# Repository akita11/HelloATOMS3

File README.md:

# HelloATOMS3

ATOMS3を使ったｽﾀｯｸﾁｬﾝ的な顔表示＋簡単なはんだ付けボード製作＋UIFlow2でのプログラミングのセットのハンズオン資料です。

## Author

Junichi Akita (akita@ifdl.jp, @akita11)

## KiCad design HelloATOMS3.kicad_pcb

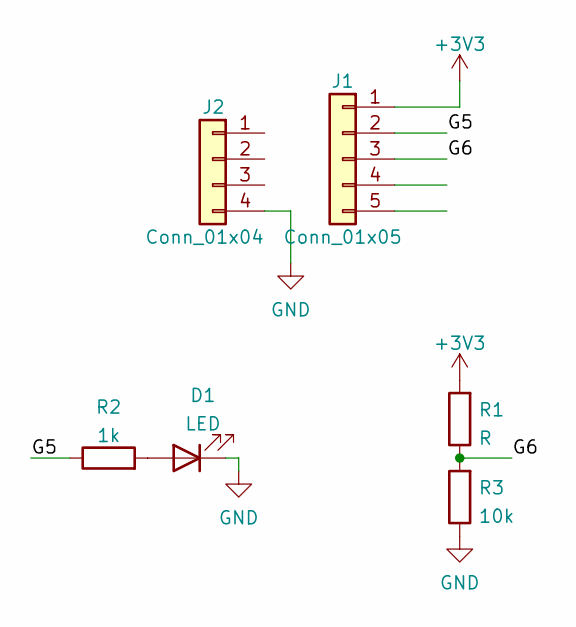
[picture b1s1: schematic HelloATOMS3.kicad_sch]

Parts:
D1: LED; LED_D5.0mm
J1: Conn_01x05; PinHeader_1x05_P2.54mm_Vertical
J2: Conn_01x04; PinHeader_1x04_P2.54mm_Vertical
R1: R; R_LDR_5.1x4.3mm_P3.4mm_Vertical
R2: 1k; R_Axial_DIN0207_L6.3mm_D2.5mm_P10.16mm_Horizontal
R3: 10k; R_Axial_DIN0204_L3.6mm_D1.6mm_P7.62mm_Horizontal

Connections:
+3V3: J1.1, R1.2
/G5: J1.2, R2.1
/G6: J1.3, R1.1, R3.2
GND: D1.1 (K), J2.4, R3.1
unnamed: D1.2 (A), R2.2

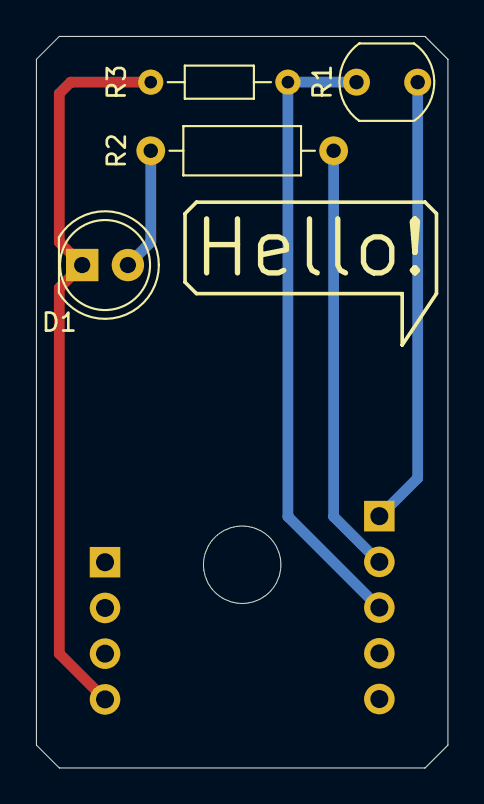
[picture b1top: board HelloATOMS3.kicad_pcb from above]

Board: 2 copper layers, 22.9 x 40.6 mm, 6 parts (0 on the bottom side), 5 nets.

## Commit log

2025-07-22 add README
